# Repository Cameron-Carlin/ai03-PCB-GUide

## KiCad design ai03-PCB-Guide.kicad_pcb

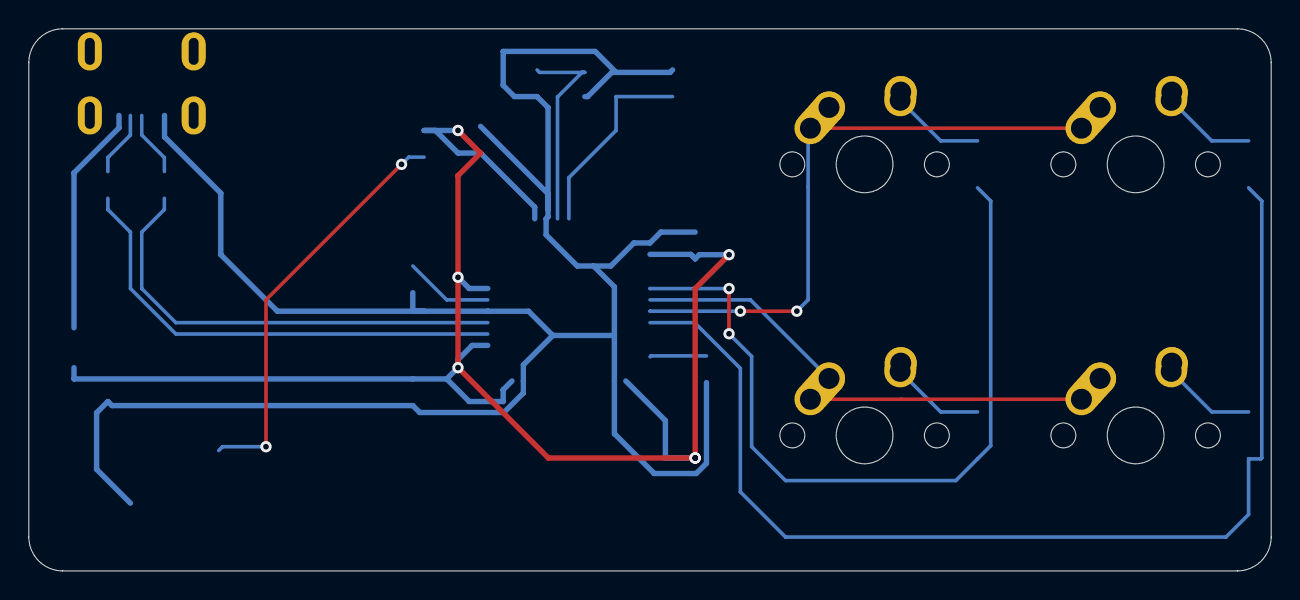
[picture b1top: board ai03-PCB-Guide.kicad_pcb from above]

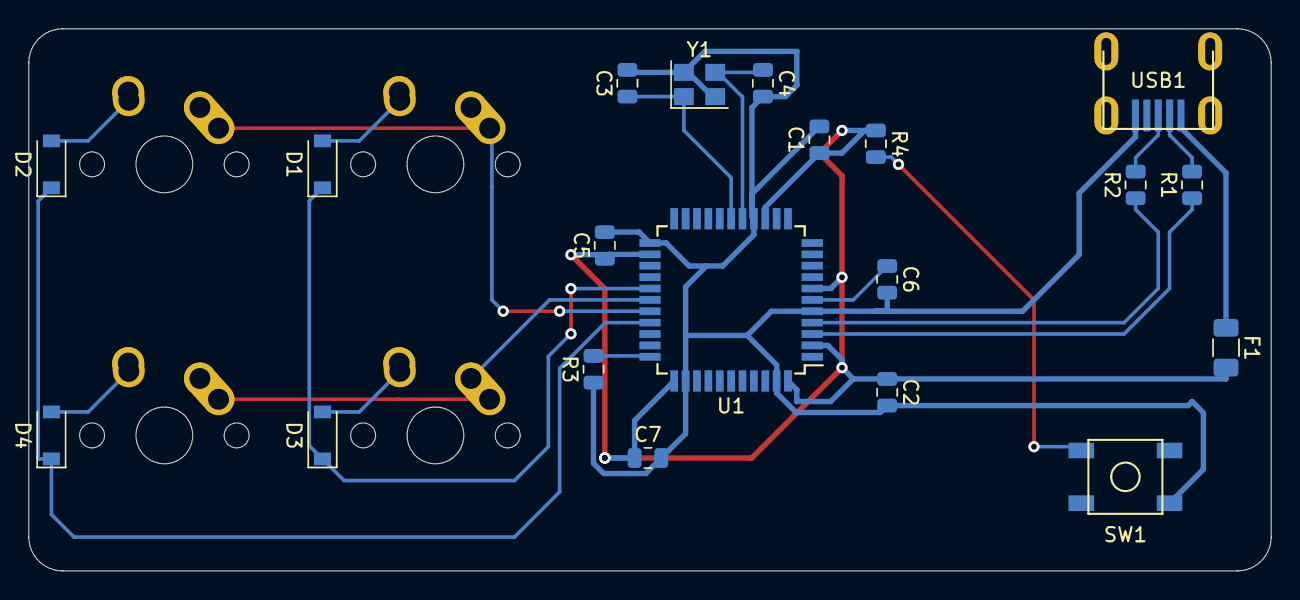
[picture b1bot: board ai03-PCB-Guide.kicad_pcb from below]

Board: 2 copper layers, 87.3 x 38.1 mm, 24 parts (20 on the bottom side), 20 nets.

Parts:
C1, C2, C5: 0.1uF; C_0805_2012Metric
C3, C4: 22pF; C_0805_2012Metric
C6: 1uF; C_0805_2012Metric
C7: 10uF; C_0805_2012Metric
D1, D2, D3, D4: D_Small; D_SOD-123
F1: 500mA; Fuse_1206_3216Metric
MX1, MX2, MX3, MX4: MX-NoLED; MX-1U-NoLED
R1, R2: 22; R_0805_2012Metric
R3, R4: 10k; R_0805_2012Metric
SW1: SW_Push; SKQG-1155865
U1: ATmega32U4-AU; TQFP-44_10x10mm_P0.8mm
USB1: Molex-0548190589
Y1: 16MHz; Crystal_SMD_3225-4Pin_3.2x2.5mm

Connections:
+5V: C1.1, C2.1, C5.1, C7.1, F1.2, R4.1, U1.2, U1.7, U1.14, U1.24, U1.34, U1.44
COL0: MX1.1, MX2.1, U1.29
COL1: MX3.1, MX4.1, U1.28
D+: R2.2, USB1.3
D-: R1.2, USB1.4
GND: C1.2, C2.2, C3.2, C4.2, C5.2, C6.2, C7.2, R3.1, SW1.1, U1.5, U1.15, U1.23, U1.35, U1.43, USB1.1, Y1.2, Y1.4
unnamed: C3.1, U1.17, Y1.1
unnamed: C4.1, U1.16, Y1.3
unnamed: C6.1, U1.6
unnamed: D1.2, MX1.2
unnamed: D2.2, MX2.2
unnamed: D3.2, MX3.2
unnamed: D4.2, MX4.2
unnamed: R1.1, U1.3
unnamed: R2.1, U1.4
unnamed: R3.2, U1.33
unnamed: R4.2, SW1.2, U1.13
ROW0: D1.1, D3.1, U1.27
ROW1: D2.1, D4.1, U1.30
VCC: F1.1, USB1.5

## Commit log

2020-06-20 Initialised Project
    Setting up the project and pushign to GIT
2020-06-20 Add submodules
2020-06-20 Added Libraries to Project
    Added the libraries the project required, and have enabled these within the keycad editor.
2020-06-20 New Libraries
    Added and activated new libraries within KiCAD
2020-06-20 Edits to PCB Schematic
    Added the ATMega Controller device, and have begun by grounding the unit and adding resistors to the USB connectors.
2020-06-20 New Capacitor
    Added the first capacitor to the board. Done by following the official documentation and the tutorial. Generally speaking it's good if you can find the official documentation and some form of proven 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
2020-06-20 Decoupling Capacitors
    This step involved making the capacitors that filter the electrical noise from the microcrontroller. The official documentation says to use 0.1uF by each VCC, which would make 4, and a 10uF overall. 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
2020-06-20 Crystals and Reset
    Added the crystals and routed to GND, also added the Reset button to allow the MCU to be put into bootloader.mm
2020-06-20 AREF Pin and Nets
    Added the AREF pin to the Reset. Also added pins to the USB (Ctrl+H allows for this) in order to make it so that I don't have to run wires across the entire schematic when moving past the MCU work.
2020-06-20 USB Circuitry
    Added the USB circuitry to be able to actually have an output for the board. It's not USB-C but that's covered later.
2020-06-20 Footprinting the Schematic
    This is done to create the associations of the components with the actual schematic that we have made. The software can do this on it's own with smaller projects, but in future do all of this manuall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
2020-06-21 Making the actual PCB
    So. I initially messed this up because I didn't realise that I hadn't put the keys in the correct order (Tthis can be changed around as long as I'm consistent with the decision I made in the beginnin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
2020-06-21 Beginning Routing
    This is the step just before the beginning of Routing. I've smoothed out the corners so as not to get cuts if it's printed. Setting a new Routing size called POWER for any power cables, and increasin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
2020-06-21 The bottom of the board
    Hadn't put all the SMD components on the underside of the board. This is infuriating as it meant I basically had to flip and completely reorganise the layout of the SMD components.
2020-06-27 PCB Finished
    It's a bit messy because of the way that I had wired everything in the schematic. and due to laziness I couldn't be bothered to change it. BUt what we have here is a finalised PCB and Schematic that 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
